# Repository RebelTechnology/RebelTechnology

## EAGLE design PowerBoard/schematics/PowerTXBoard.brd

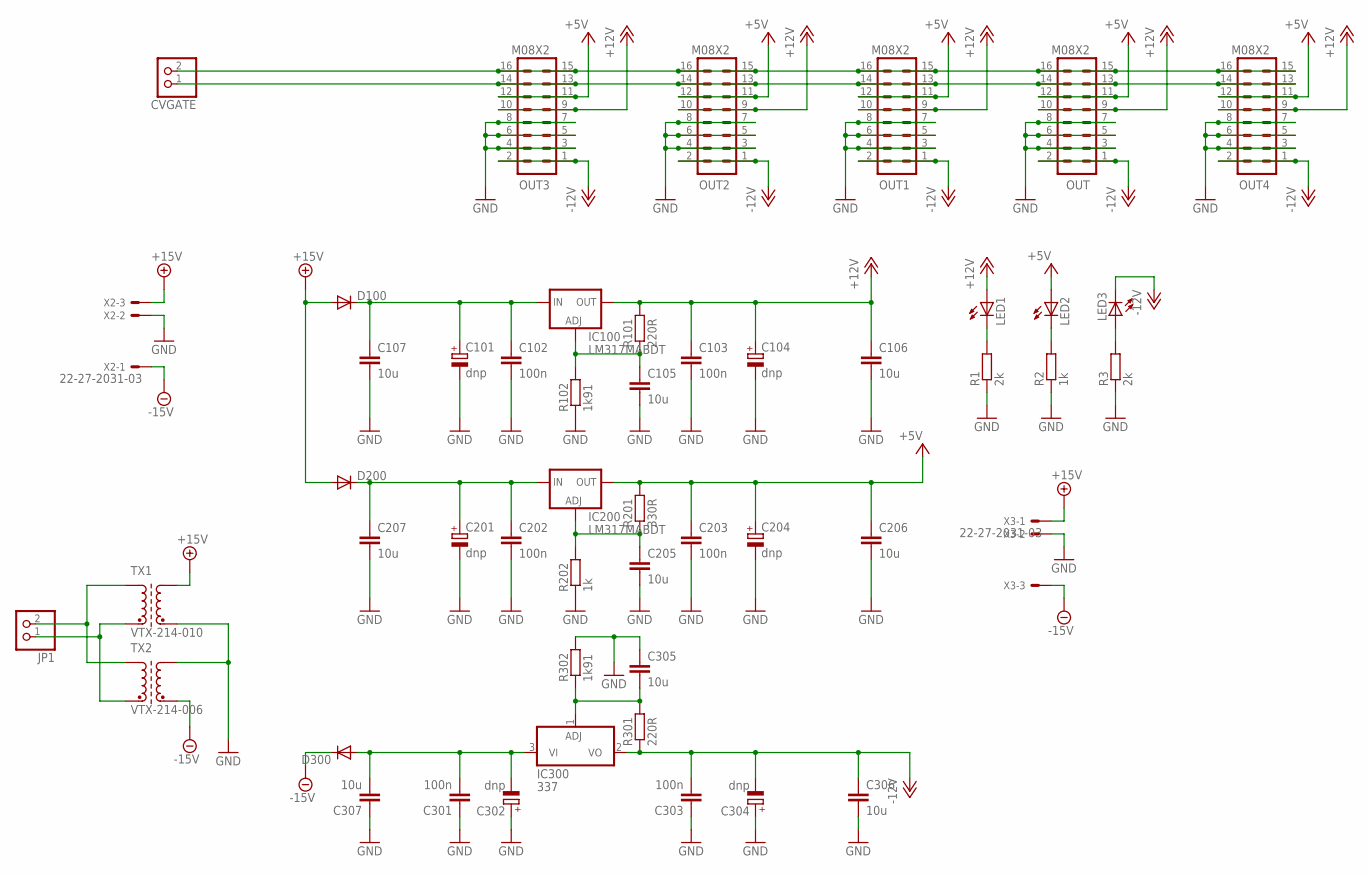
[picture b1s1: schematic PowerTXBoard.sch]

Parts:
C101, C104, C201, C204, C302, C304: dnp; CPOL-5
C102, C103, C202, C203, C301, C303: 100n; C0603
C105, C106, C107, C205, C206, C207, C305, C306, C307: 10u; C1206
CVGATE: PINHD-1X2; 1X02
D100, D200, D300: DIODESMA; SMA-DIODE
IC100, IC200: LM317MABDT; DPACK
IC300: 337; TO252
JP1: PINHD-1X2; 1X02
LED1, LED2, LED3: LEDCHIPLED_1206; CHIPLED_1206
OUT, OUT1, OUT2, OUT3, OUT4: M08X2; 2X8
R1, R3: 2k; 0603
R2, R202: 1k; 0603
R101, R301: 220R; 0603
R102, R302: 1k91; 0603
R201: 330R; 0603
TX1: VTX-214-010; VTX-214-006
TX2: VTX-214-006
X2, X3: 22-27-2031-03; 6410-03

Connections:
+5V: C203.1, C204.+, C206.1, IC200.4 (OUT), LED2.A, OUT.11, OUT.12, OUT1.11, OUT1.12, OUT2.11, OUT2.12, OUT3.11, OUT3.12, OUT4.11, OUT4.12, R201.2
+12V: C103.1, C104.+, C106.1, IC100.4 (OUT), LED1.A, OUT.9, OUT.10, OUT1.9, OUT1.10, OUT2.9, OUT2.10, OUT3.9, OUT3.10, OUT4.9, OUT4.10, R101.2
+15V: D100.A, D200.A, TX1.P$3 (A2), X2.3, X3.1
-12V: C303.2, C304.-, C306.1, IC300.2 (VO), LED3.C, OUT.1, OUT.2, OUT1.1, OUT1.2, OUT2.1, OUT2.2, OUT3.1, OUT3.2, OUT4.1, OUT4.2, R301.1
-15V: D300.C, TX2.P$4 (E2), X2.1, X3.3
GND: C101.-, C102.2, C103.2, C104.-, C105.2, C106.2, C107.2, C201.-, C202.2, C203.2, C204.-, C205.2, C206.2, C207.2, C301.1, C302.+, C303.1, C304.+, C305.1, C306.2, C307.1, OUT.3, OUT.4, OUT.5, OUT.6, OUT.7, OUT.8, OUT1.3, OUT1.4, OUT1.5, OUT1.6, OUT1.7, OUT1.8, OUT2.3, OUT2.4, OUT2.5, OUT2.6, OUT2.7, OUT2.8, OUT3.3, OUT3.4, OUT3.5, OUT3.6, OUT3.7, OUT3.8, OUT4.3, OUT4.4, OUT4.5, OUT4.6, OUT4.7, OUT4.8, R1.1, R2.1, R3.1, R102.1, R202.1, R302.2, TX1.P$4 (E2), TX2.P$3 (A2), X2.2, X3.2
unnamed: LED1.C, R1.2
unnamed: LED2.C, R2.2
unnamed: C105.1, IC100.1 (ADJ), R101.1, R102.2
unnamed: C205.1, IC200.1 (ADJ), R201.1, R202.2
unnamed: C305.2, IC300.1 (ADJ), R301.2, R302.1
unnamed: C301.2, C302.-, C307.2, D300.A, IC300.3 (VI)
unnamed: C201.+, C202.1, C207.1, D200.C, IC200.3 (IN)
unnamed: C101.+, C102.1, C107.1, D100.C, IC100.3 (IN)
unnamed: LED3.A, R3.2
unnamed: CVGATE.1, OUT.13, OUT.14, OUT1.13, OUT1.14, OUT2.13, OUT2.14, OUT3.13, OUT3.14, OUT4.13, OUT4.14
unnamed: JP1.2, TX1.P$1 (A1), TX2.P$1 (A1)
unnamed: CVGATE.2, OUT.15, OUT.16, OUT1.15, OUT1.16, OUT2.15, OUT2.16, OUT3.15, OUT3.16, OUT4.15, OUT4.16
unnamed: JP1.1, TX1.P$2 (E1), TX2.P$2 (E1)

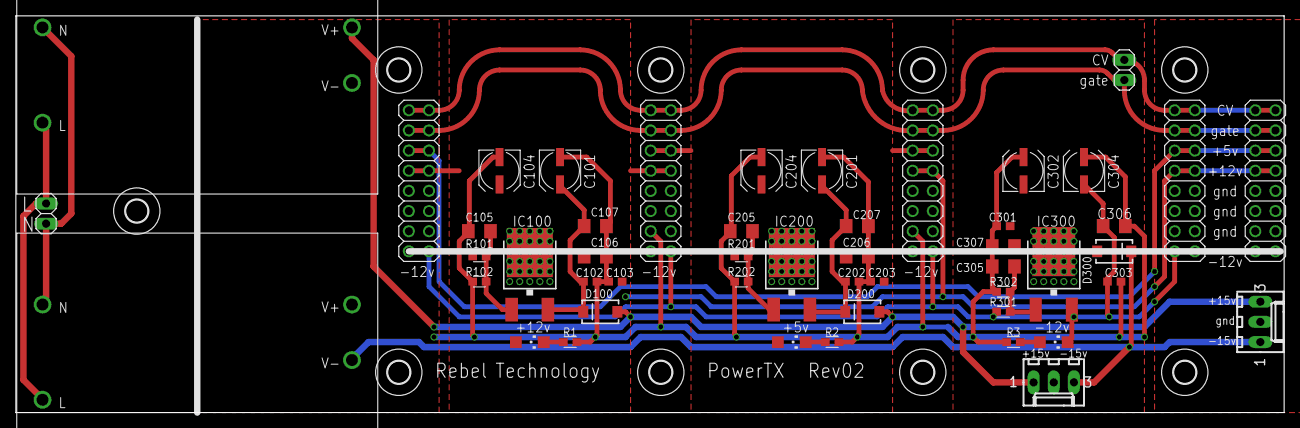
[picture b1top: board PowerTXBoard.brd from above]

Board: 2 copper layers, 159.8 x 50.0 mm, 59 parts (0 on the bottom side), 19 nets.

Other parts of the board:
U$1, U$2, U$3, U$4, U$5, U$6, U$7, U$8, U$11: 2,8

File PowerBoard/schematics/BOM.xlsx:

Qty | Value | Device | Parts | Description
3 |  | DIODESMA | D100, D200, D300 | Diode
3 |  | LEDCHIPLED_1206 | LED1, LED2, LED3 | LED
3 | 100n | C-EUC0603 | C102, C202, C301 | CAPACITOR, European symbol
6 | 10u | CPOL-EU153CLV-0810 | C101, C104, C201, C204, C302, C304 | POLARIZED CAPACITOR, European symbol
4 | 1k | R-EU_0603 | R2, R202 | RESISTOR, European symbol
3 | 1u | C-EUC0603 | C103, C203, C303 | CAPACITOR, European symbol
4 | 22-27-2031-03 | 22-27-2031-03 | X1, X2, X3, X4 | CONNECTOR
2 | 220R | R-EU_0603 | R101, R301 | RESISTOR, European symbol
2 | 1.91k | R-EU_0603 | R102, R302 | RESISTOR, European symbol
1 | 330R | R-EU_0603 | R201 | RESISTOR, European symbol
1 | LM337 | TO252 | IC300 | Negative VOLTAGE REGULATOR
2 | LM317MABDT | LM317MABDT | IC100, IC200 | 500 mA Adjustable Output Positive Voltage Regulator
6 | M08X2 | M08X2 | OUT, OUT1, OUT2, OUT3, OUT4, OUT5
6 | dnp | CPOL-EUE5-8.5 | C100, C105, C200, C205, C300, C305 | POLARIZED CAPACITOR, European symbol
2 | 2k | R-EU_0603 | R1, R3 | RESISTOR, European symbol

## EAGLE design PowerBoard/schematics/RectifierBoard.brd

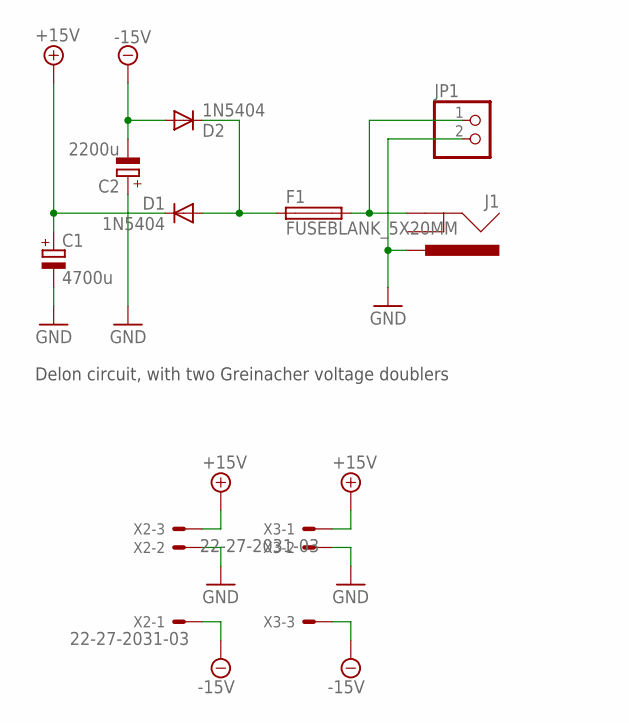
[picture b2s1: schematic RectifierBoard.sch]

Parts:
C1: 4700u; E7,5-18
C2: 2200u; E7,5-18
D1, D2: 1N5404; DIODE-1N4001
F1: FUSEBLANK_5X20MM; FUSE_HOLDER_5X20MM
J1: POWER_JACKPTH; POWER_JACK_PTH
JP1: PINHD-1X2; 1X02
X2, X3: 22-27-2031-03; 6410-03

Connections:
+15V: C1.+, D1.C, X2.3, X3.1
-15V: C2.-, D2.A, X2.1, X3.3
GND: C1.-, C2.+, J1.PWR, JP1.2, X2.2, X3.2
unnamed: D1.A, D2.C, F1.1
unnamed: F1.2, J1.GND, JP1.1

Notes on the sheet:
Delon circuit, with two Greinacher voltage doublers

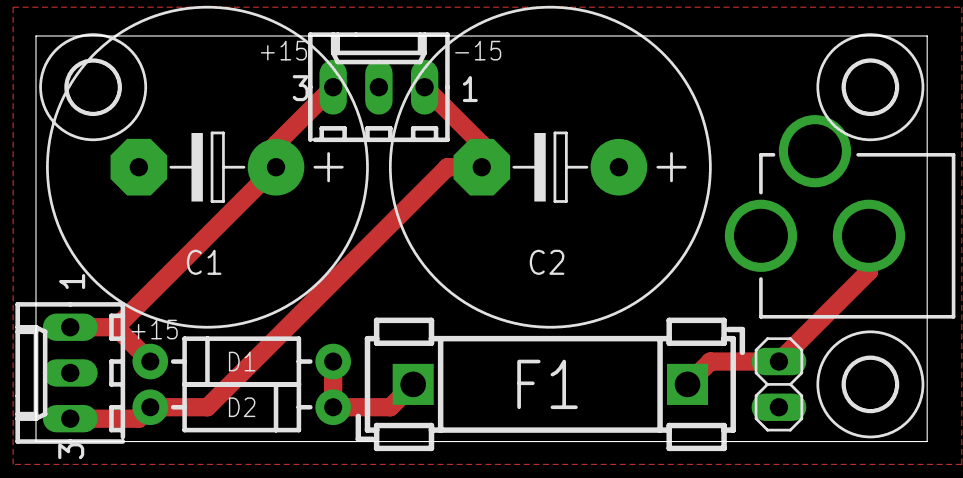
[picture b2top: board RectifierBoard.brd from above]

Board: 2 copper layers, 49.5 x 22.5 mm, 12 parts (0 on the bottom side), 5 nets.

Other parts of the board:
U$1, U$2, U$3: 2,8

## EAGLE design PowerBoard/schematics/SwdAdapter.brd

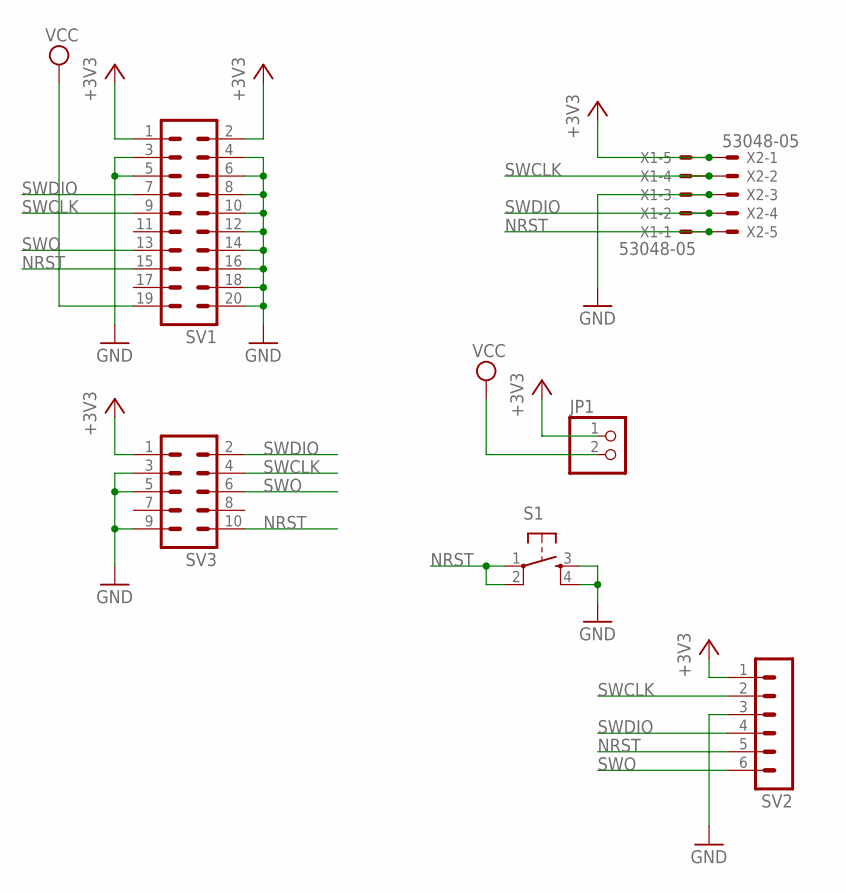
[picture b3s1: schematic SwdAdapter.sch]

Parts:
JP1: PINHD-1X2; 1X02
S1: TAC_SWITCHPTH; TACTILE-PTH
SV1: MA10-2
SV2: MA06-1
SV3: MA05-2
X1, X2: 53048-05

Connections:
+3V3: JP1.1, SV1.1, SV1.2, SV2.1, SV3.1, X1.5, X2.1
GND: S1.3, S1.4, SV1.3, SV1.4, SV1.5, SV1.6, SV1.8, SV1.10, SV1.12, SV1.14, SV1.16, SV1.18, SV1.20, SV2.3, SV3.3, SV3.5, SV3.9, X1.3, X2.3
NRST: S1.1, S1.2, SV1.15, SV2.5, SV3.10, X1.1, X2.5
SWCLK: SV1.9, SV2.2, SV3.4, X1.4, X2.2
SWDIO: SV1.7, SV2.4, SV3.2, X1.2, X2.4
SWO: SV1.13, SV2.6, SV3.6
VCC: JP1.2, SV1.19

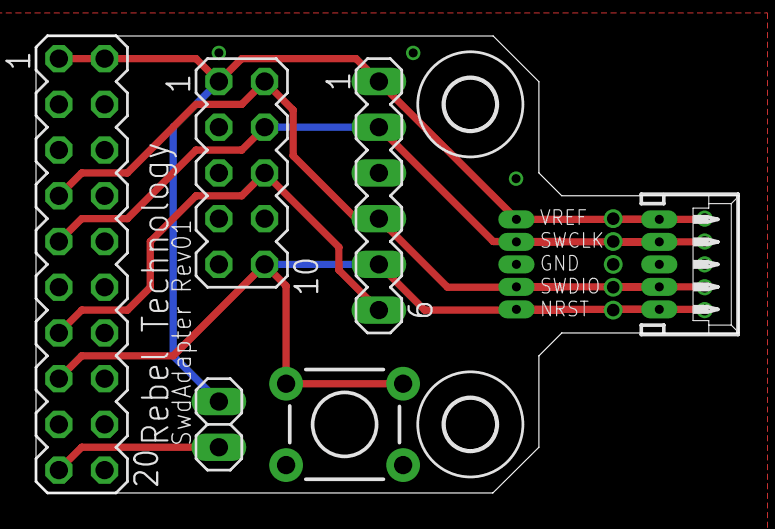
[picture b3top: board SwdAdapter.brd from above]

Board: 2 copper layers, 39.1 x 25.4 mm, 9 parts (1 on the bottom side), 7 nets.

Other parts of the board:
U$1, U$5: 2,8

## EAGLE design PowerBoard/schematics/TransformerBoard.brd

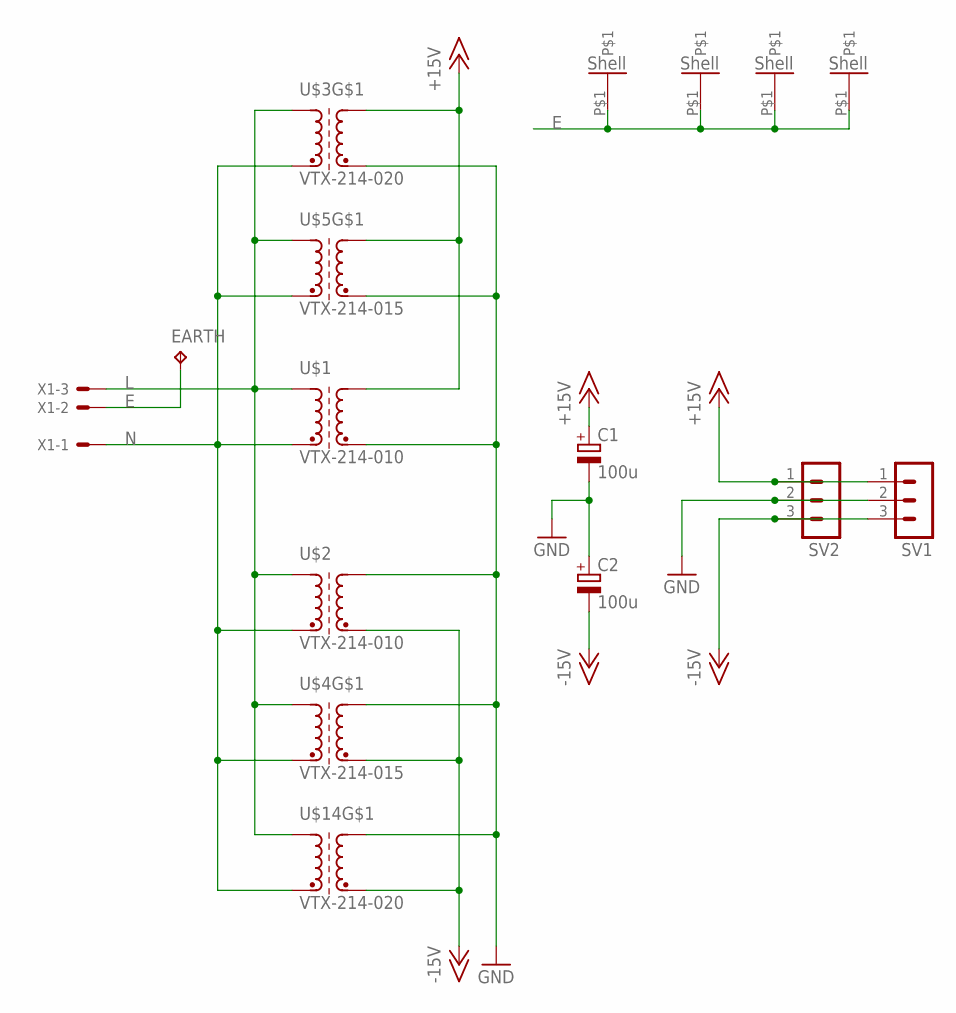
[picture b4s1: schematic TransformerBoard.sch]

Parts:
C1, C2: 100u; E5-8,5
EARTH: TPPAD1-17; P1-17
SV1, SV2: MA03-1
U$1, U$2: VTX-214-010
U$3, U$14: VTX-214-020
U$4, U$5: VTX-214-015
X1: KK-156-3

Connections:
+15V: C1.+, SV1.1, SV2.1, U$1.P$3 (A2), U$3.P$4 (A2), U$5.P$4 (A2)
-15V: C2.-, SV1.3, SV2.3, U$2.P$4 (E2), U$4.P$5 (E2), U$14.P$5 (E2)
E: EARTH.TP, U$3.P$1, U$4.P$1, U$5.P$1, U$14.P$1, X1.2
GND: C1.-, C2.+, SV1.2, SV2.2, U$1.P$4 (E2), U$2.P$3 (A2), U$3.P$5 (E2), U$4.P$4 (A2), U$5.P$5 (E2), U$14.P$4 (A2)
L: U$1.P$1 (A1), U$2.P$1 (A1), U$3.P$3 (A1), U$4.P$3 (A1), U$5.P$3 (A1), U$14.P$3 (A1), X1.3
N: U$1.P$2 (E1), U$2.P$2 (E1), U$3.P$2 (E1), U$4.P$2 (E1), U$5.P$2 (E1), U$14.P$2 (E1), X1.1

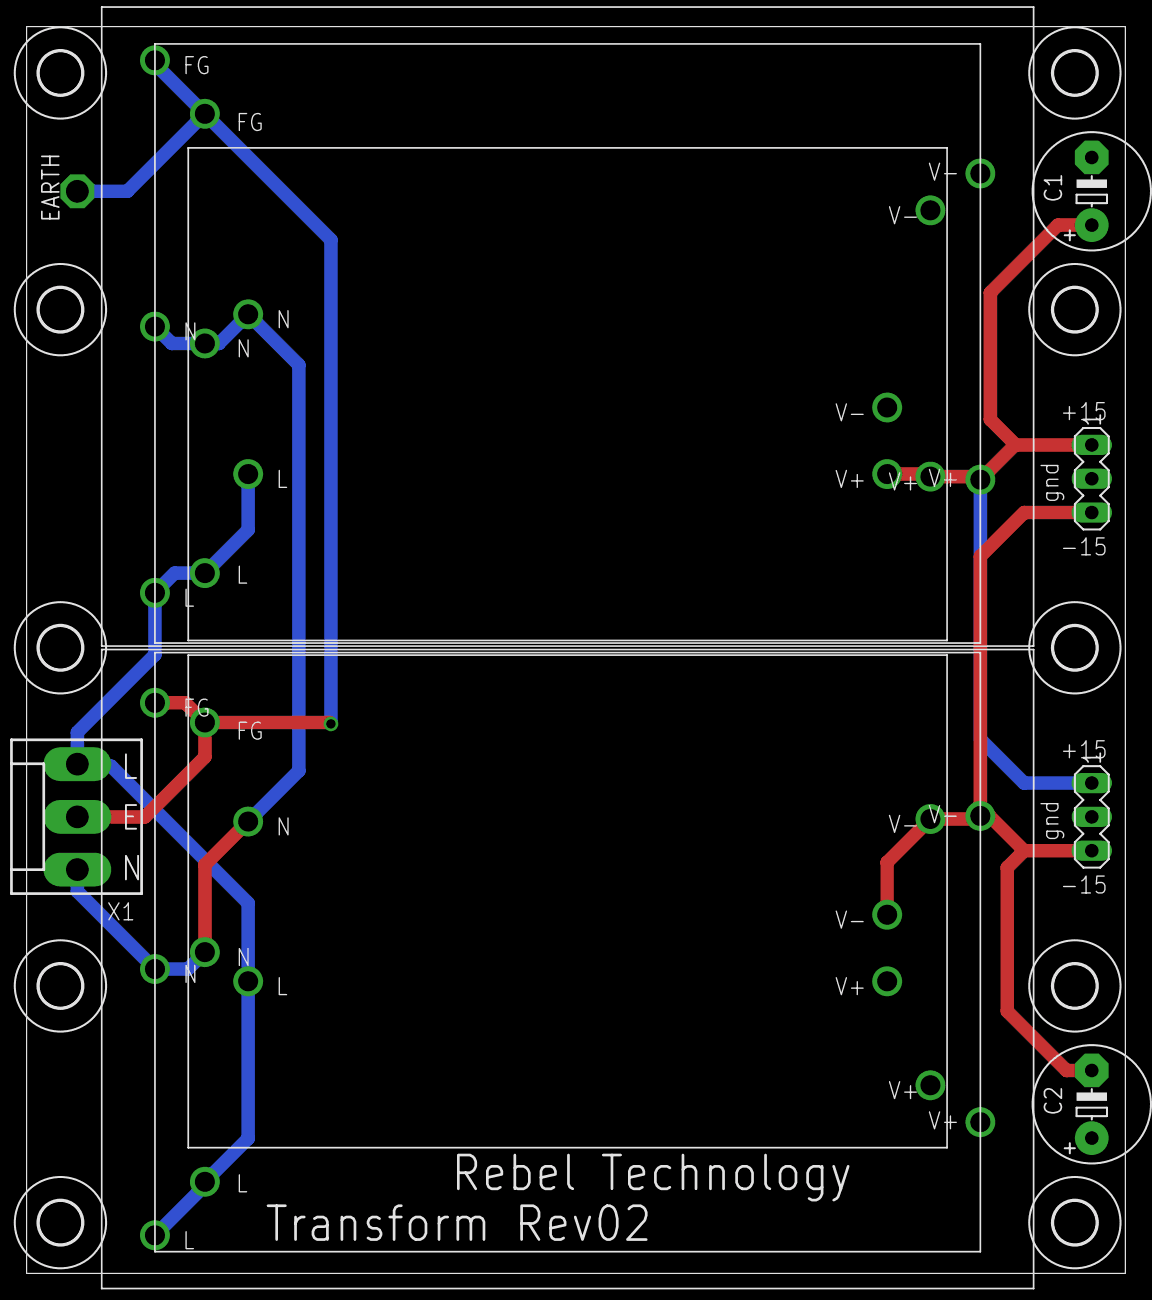
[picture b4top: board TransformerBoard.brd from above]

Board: 2 copper layers, 82.5 x 93.7 mm, 22 parts (0 on the bottom side), 6 nets.

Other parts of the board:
U$6, U$7, U$8, U$9, U$10, U$11, U$12, U$13, U$15, U$16: 3,2

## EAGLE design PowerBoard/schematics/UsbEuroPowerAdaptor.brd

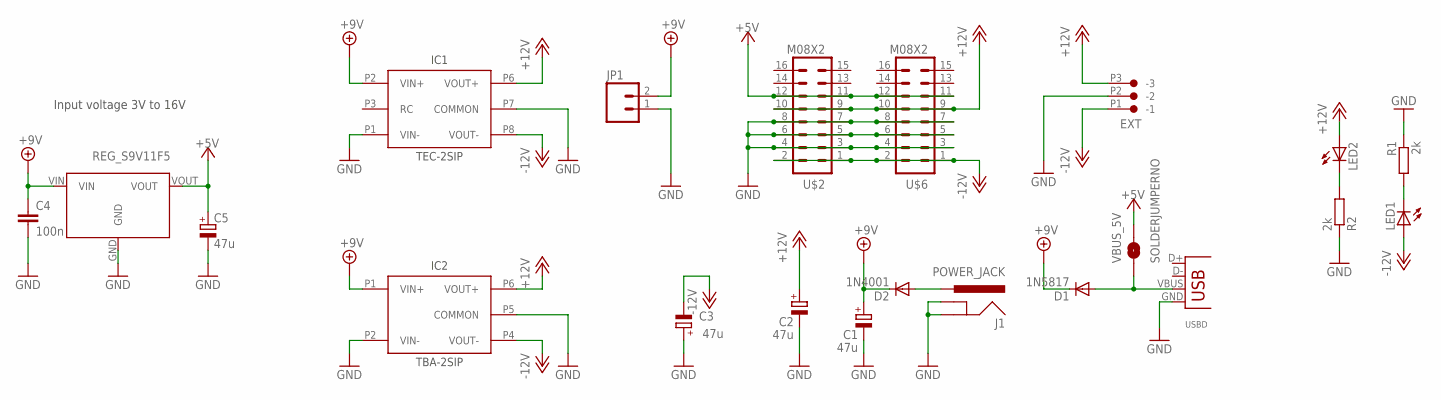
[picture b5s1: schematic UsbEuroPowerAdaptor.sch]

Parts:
C1, C2, C3, C5: 47u; E5-6
C4: 100n; C050-024X044
D1: 1N5817; DIODE-1N4001
D2: 1N4001; DIODE-1N4001
EXT: CON-JST_PH_3W
IC1: TEC-2SIP; TEC-2
IC2: TBA-2SIP; TBA-2
IC3: REG_S9V11F5
J1: POWER_JACK; DC_JACK_SLOT
JP1: M02PTH; 1X02
LED1, LED2: LED3MM
R1, R2: 2k; 0204/7
U$2, U$6: M08X2; 2X8
USBD: USB-B-H
VBUS_5V: SOLDERJUMPERNO; SJ_2S-NO

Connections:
+5V: C5.+, IC3.VOUT, U$2.11, U$2.12, U$6.11, U$6.12, VBUS_5V.2
+9V: C1.+, C4.1, D1.C, D2.C, IC1.P2 (VIN+), IC2.P1 (VIN+), IC3.VIN, JP1.2
+12V: C2.+, EXT.P3 (-3), IC1.P6 (VOUT+), IC2.P6 (VOUT+), LED2.A, U$2.9, U$2.10, U$6.9, U$6.10
-12V: C3.-, EXT.P1 (-1), IC1.P8 (VOUT-), IC2.P4 (VOUT-), LED1.A, U$2.1, U$2.2, U$6.1, U$6.2
EXT_USB_D_VBUS: D1.A, USBD.VBUS, VBUS_5V.1
GND: C1.-, C2.-, C3.+, C4.2, C5.-, EXT.P2 (-2), IC1.P1 (VIN-), IC1.P7 (COMMON), IC2.P2 (VIN-), IC2.P5 (COMMON), IC3.GND, J1.GND, J1.GNDBREAK, JP1.1, R1.1, R2.1, U$2.3, U$2.4, U$2.5, U$2.6, U$2.7, U$2.8, U$6.3, U$6.4, U$6.5, U$6.6, U$6.7, U$6.8, USBD.GND
unnamed: LED2.K (C), R2.2
unnamed: LED1.K (C), R1.2
unnamed: D2.A, J1.PWR

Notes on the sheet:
Input voltage 3V to 16V

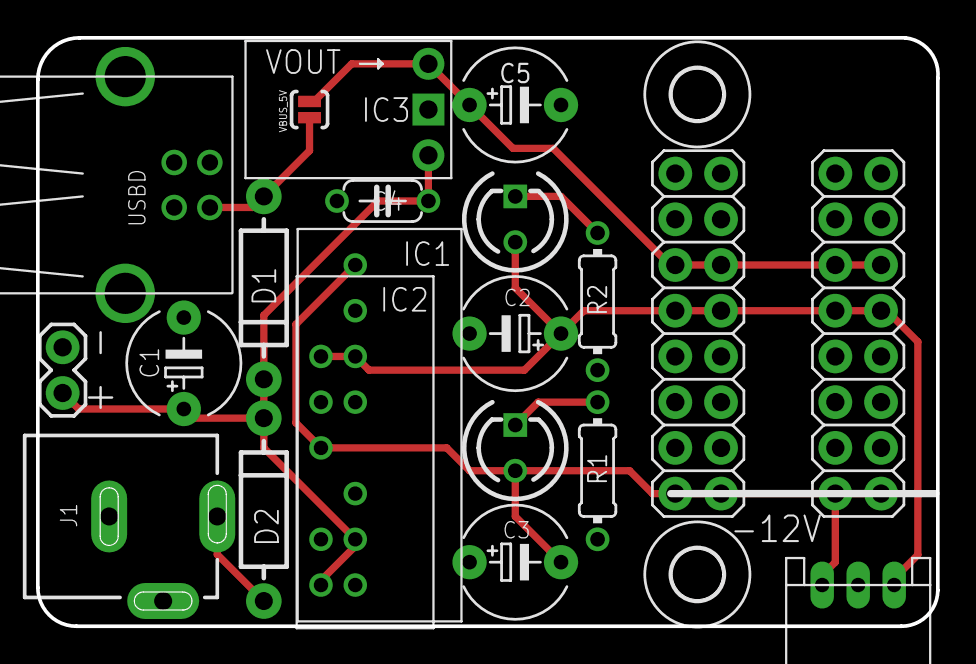
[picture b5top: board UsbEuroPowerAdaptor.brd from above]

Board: 2 copper layers, 50.0 x 32.7 mm, 23 parts (0 on the bottom side), 9 nets.

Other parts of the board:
U$1, U$3: 2,8

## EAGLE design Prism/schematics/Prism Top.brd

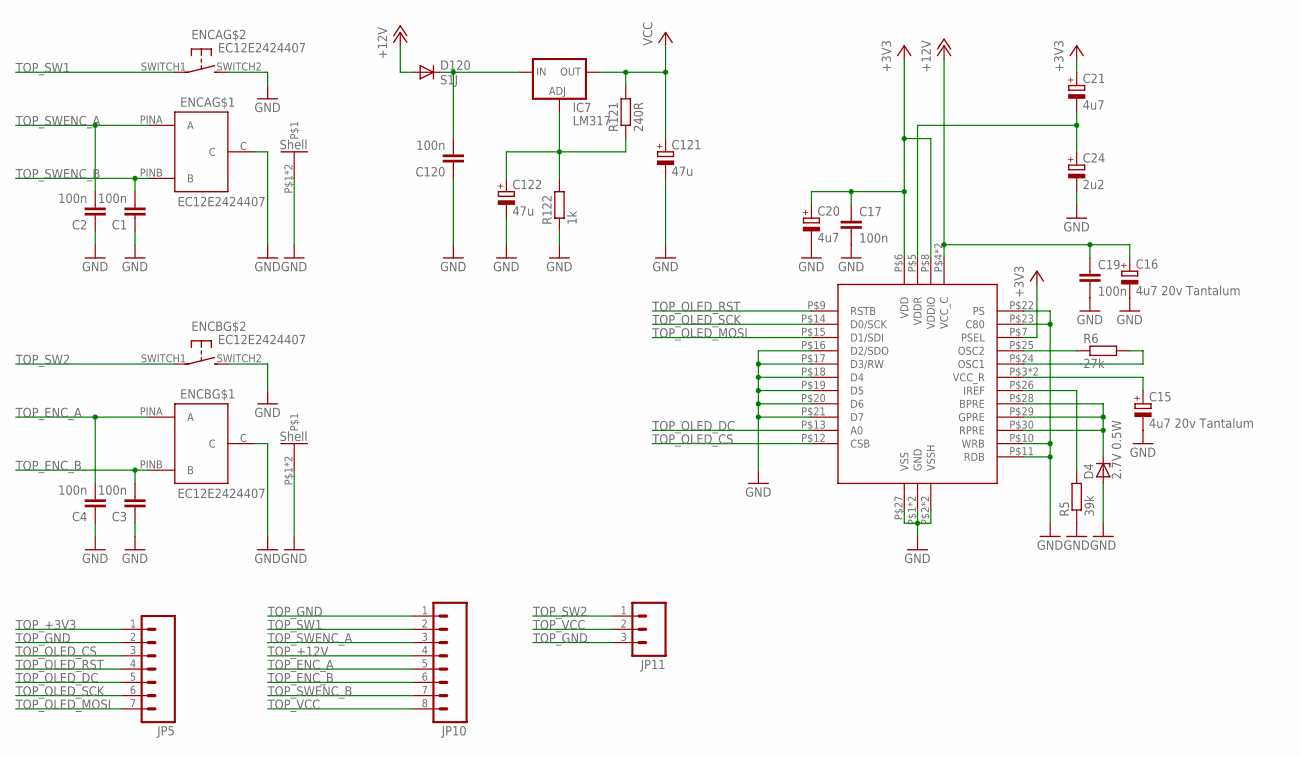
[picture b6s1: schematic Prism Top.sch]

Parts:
C1, C2, C3, C4, C17, C19, C120: 100n; C0603
C15, C16: 4u7 20v Tantalum; CT3216
C20, C21: 4u7; 153CLV-0405
C24: 2u2; 153CLV-0405
C121, C122: 47u; CPOL-5
D4: 2.7V 0.5W; SOD80C
D120: S1J; SMA-DIODE
ENCA: EC12E2424407
ENCB: EC12E2424407
IC7: LM317; DPACK
JP5: M07; 1X07
JP10: M081X08; 1X08
JP11: M03PTH; 1X03
R5: 39k; 0603
R6: 27k; 0603
R121: 240R; 0603
R122: 1k; 0603
U$1: MCOT096096AY

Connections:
unnamed: C120.2, D120.C, IC7.3 (IN)
unnamed: C15.+, U$1.P$3 (VCC_R), U$1.P$32 (VCC_R)
unnamed: C122.+, IC7.1 (ADJ), R121.1, R122.2
unnamed: C21.-, C24.+, U$1.P$5 (VDDR)
unnamed: D4.C, U$1.P$28 (BPRE), U$1.P$29 (GPRE), U$1.P$30 (RPRE)
unnamed: R6.1, U$1.P$25 (OSC2)
unnamed: R6.2, U$1.P$24 (OSC1)
unnamed: R5.2, U$1.P$26 (IREF)
TOP_+3V3: C17.1, C20.+, C21.+, JP5.1, U$1.P$6 (VDD), U$1.P$7 (PSEL), U$1.P$8 (VDDIO)
TOP_+12V: C16.+, C19.1, D120.A, JP10.4, U$1.P$4 (VCC_C), U$1.P$31 (VCC_C)
TOP_ENC_A: C4.2, ENCB.PINA (A), JP10.5
TOP_ENC_B: C3.2, ENCB.PINB (B), JP10.6
TOP_GND: C1.1, C2.1, C3.1, C4.1, C15.-, C16.-, C17.2, C19.2, C20.-, C24.-, C120.1, C121.-, C122.-, D4.A, ENCA.C, ENCA.P$1, ENCA.P$2, ENCA.SWITCH2 (S), ENCB.C, ENCB.P$1, ENCB.P$2, ENCB.SWITCH2 (S), JP5.2, JP10.1, JP11.3, R5.1, R122.1, U$1.P$1 (GND), U$1.P$2 (VSSH), U$1.P$10 (WRB), U$1.P$11 (RDB), U$1.P$16 (D2/SDO), U$1.P$17 (D3/RW), U$1.P$18 (D4), U$1.P$19 (D5), U$1.P$20 (D6), U$1.P$21 (D7), U$1.P$22 (PS), U$1.P$23 (C80), U$1.P$27 (VSS), U$1.P$33 (VSSH), U$1.P$34 (GND)
TOP_OLED_CS: JP5.3, U$1.P$12 (CSB)
TOP_OLED_DC: JP5.5, U$1.P$13 (A0)
TOP_OLED_MOSI: JP5.7, U$1.P$15 (D1/SDI)
TOP_OLED_RST: JP5.4, U$1.P$9 (RSTB)
TOP_OLED_SCK: JP5.6, U$1.P$14 (D0/SCK)
TOP_SW1: ENCA.SWITCH1, JP10.2
TOP_SW2: ENCB.SWITCH1, JP11.1
TOP_SWENC_A: C2.2, ENCA.PINA (A), JP10.3
TOP_SWENC_B: C1.2, ENCA.PINB (B), JP10.7
TOP_VCC: C121.+, IC7.4 (OUT), JP10.8, JP11.2, R121.2

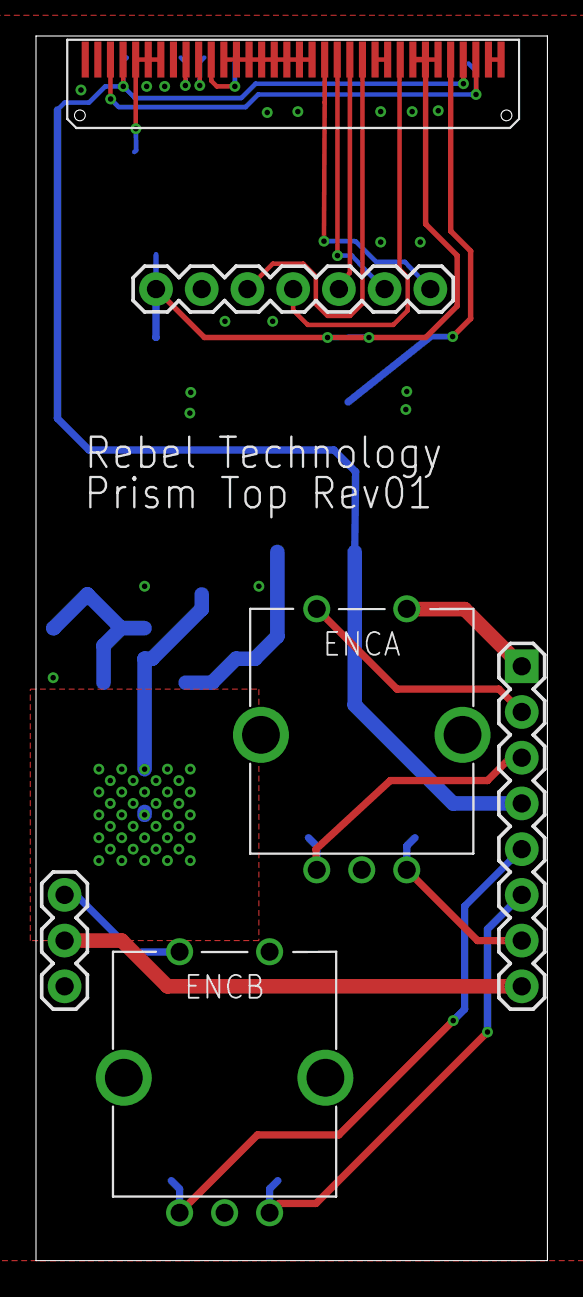
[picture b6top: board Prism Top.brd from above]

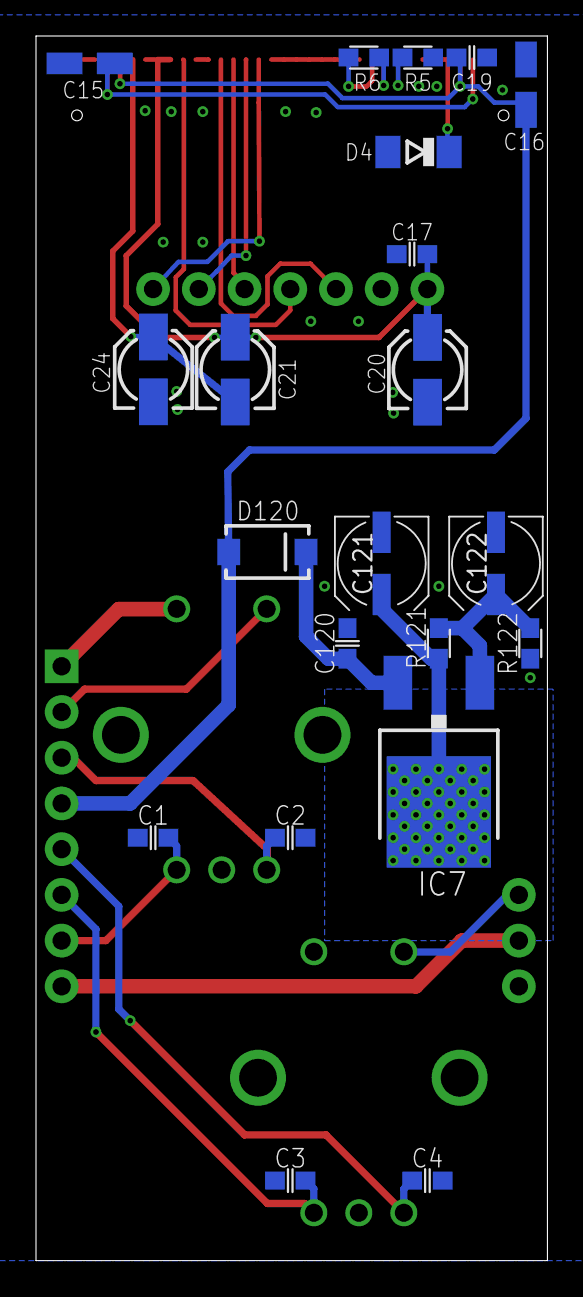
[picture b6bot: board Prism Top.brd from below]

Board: 2 copper layers, 28.4 x 68.0 mm, 27 parts (21 on the bottom side), 23 nets.

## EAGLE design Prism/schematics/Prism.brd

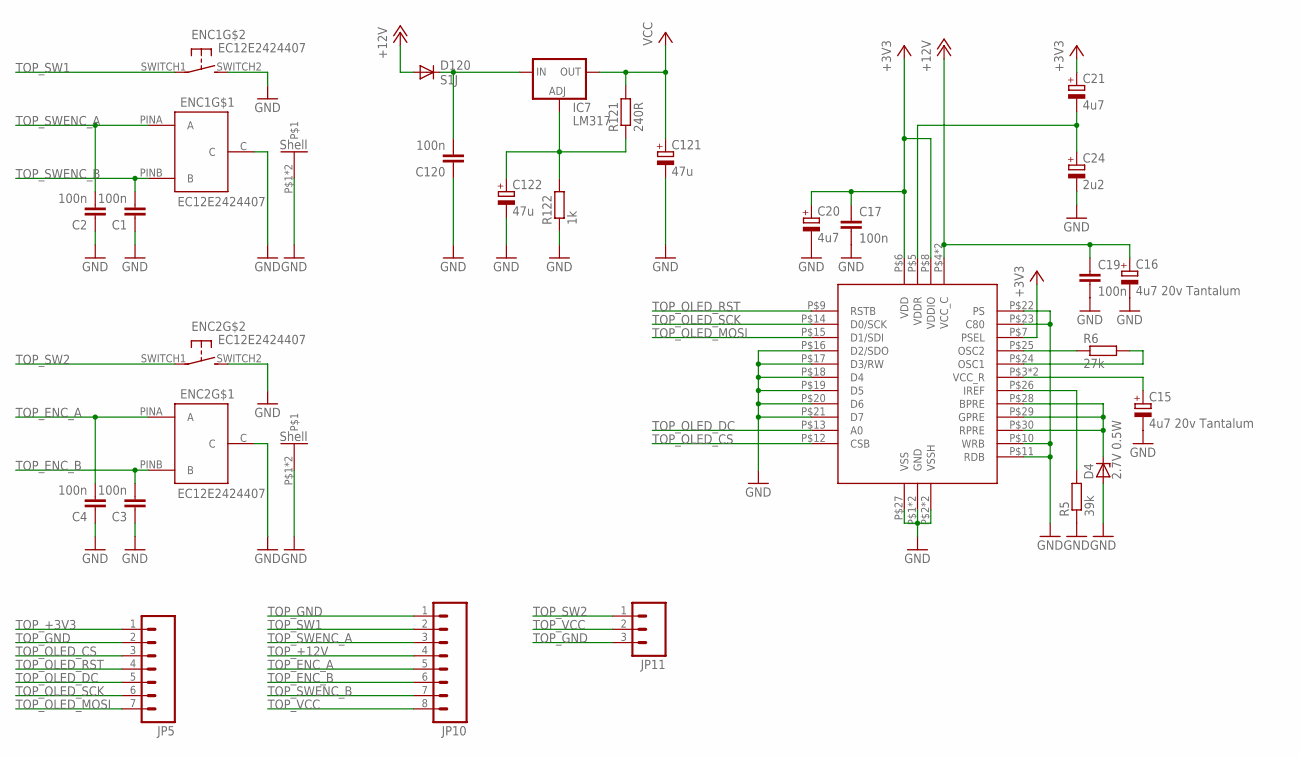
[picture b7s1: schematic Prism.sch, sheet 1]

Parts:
C1, C2, C3, C4, C17, C19, C120: 100n; C0603
C15, C16: 4u7 20v Tantalum; CT3216
C20, C21: 4u7; 153CLV-0405
C24: 2u2; 153CLV-0405
C121, C122: 47u; CPOL-5
D4: 2.7V 0.5W; SOD80C
D120: S1J; SMA-DIODE
ENC1, ENC2: EC12E2424407
IC7: LM317; DPACK
JP5: M07; 1X07
JP10: M081X08; 1X08
JP11: M03PTH; 1X03
R5: 39k; 0603
R6: 27k; 0603
R121: 240R; 0603
R122: 1k; 0603
U$1: MCOT096096AY

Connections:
unnamed: C120.2, D120.C, IC7.3 (IN)
unnamed: C15.+, U$1.P$3 (VCC_R), U$1.P$32 (VCC_R)
unnamed: C122.+, IC7.1 (ADJ), R121.1, R122.2
unnamed: C21.-, C24.+, U$1.P$5 (VDDR)
unnamed: D4.C, U$1.P$28 (BPRE), U$1.P$29 (GPRE), U$1.P$30 (RPRE)
unnamed: R6.1, U$1.P$25 (OSC2)
unnamed: R6.2, U$1.P$24 (OSC1)
unnamed: R5.2, U$1.P$26 (IREF)
TOP_+3V3: C17.1, C20.+, C21.+, JP5.1, U$1.P$6 (VDD), U$1.P$7 (PSEL), U$1.P$8 (VDDIO)
TOP_+12V: C16.+, C19.1, D120.A, JP10.4, U$1.P$4 (VCC_C), U$1.P$31 (VCC_C)
TOP_ENC_A: C4.2, ENC2.PINA (A), JP10.5
TOP_ENC_B: C3.2, ENC2.PINB (B), JP10.6
TOP_GND: C1.1, C2.1, C3.1, C4.1, C15.-, C16.-, C17.2, C19.2, C20.-, C24.-, C120.1, C121.-, C122.-, D4.A, ENC1.C, ENC1.P$1, ENC1.P$2, ENC1.SWITCH2 (S), ENC2.C, ENC2.P$1, ENC2.P$2, ENC2.SWITCH2 (S), JP5.2, JP10.1, JP11.3, R5.1, R122.1, U$1.P$1 (GND), U$1.P$2 (VSSH), U$1.P$10 (WRB), U$1.P$11 (RDB), U$1.P$16 (D2/SDO), U$1.P$17 (D3/RW), U$1.P$18 (D4), U$1.P$19 (D5), U$1.P$20 (D6), U$1.P$21 (D7), U$1.P$22 (PS), U$1.P$23 (C80), U$1.P$27 (VSS), U$1.P$33 (VSSH), U$1.P$34 (GND)
TOP_OLED_CS: JP5.3, U$1.P$12 (CSB)
TOP_OLED_DC: JP5.5, U$1.P$13 (A0)
TOP_OLED_MOSI: JP5.7, U$1.P$15 (D1/SDI)
TOP_OLED_RST: JP5.4, U$1.P$9 (RSTB)
TOP_OLED_SCK: JP5.6, U$1.P$14 (D0/SCK)
TOP_SW1: ENC1.SWITCH1, JP10.2
TOP_SW2: ENC2.SWITCH1, JP11.1
TOP_SWENC_A: C2.2, ENC1.PINA (A), JP10.3
TOP_SWENC_B: C1.2, ENC1.PINB (B), JP10.7
TOP_VCC: C121.+, IC7.4 (OUT), JP10.8, JP11.2, R121.2

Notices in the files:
parts and their libraries:
SparkFun: Licensing: CC v3.0 Share-Alike You are welcome to use this library for commercial purposes.
